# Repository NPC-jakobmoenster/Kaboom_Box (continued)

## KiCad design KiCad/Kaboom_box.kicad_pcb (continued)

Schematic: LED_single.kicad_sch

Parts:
LED104, LED105, LED106: KT-0603R; LED0603-RD; LCSC C2286
R155, R156, R157: 0603WAF2000T5E; R0603; LCSC C8218
U121, U122: 2N7002; SOT-23-3_L2.9-W1.3-P1.90-LS2.4-BR; LCSC C8545

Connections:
/Bottom/LEDs_Bottom/LEDS_discreet/LED_single1/LED_GREEN: U122.1 (G); also elsewhere on the board
/Bottom/LEDs_Bottom/LEDS_discreet/LED_single1/LED_RED: U121.1 (G); also elsewhere on the board
/Bottom/LEDs_Bottom/VDD: R155.2, R156.2, R157.2; also elsewhere on the board
GND: U121.2 (S), U122.2 (S); also elsewhere on the board
unnamed: LED104.2 (A), R155.1
unnamed: LED104.1 (K), LED105.1 (K), U121.3 (D)
unnamed: LED105.2 (A), R156.1
unnamed: LED106.2 (A), R157.1
unnamed: LED106.1 (K), U122.3 (D)

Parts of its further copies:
LED109, LED110, LED111, LED112, LED113, LED114, LED115, LED116, LED117, LED118, LED119, LED120, LED121, LED122, LED123, LED124, LED125, LED126, LED127, LED128, LED129, LED130, LED131, LED132, LED133, LED134, LED135, LED136, LED137, LED138, LED139, LED140, LED141, LED142, LED143, LED144, LED145, LED146, LED147, LED148, LED149, LED150, LED151, LED152, LED153, LED154, LED155, LED156, LED157, LED158, LED159, LED160, LED161, LED162, LED163, LED164, LED165, LED166, LED167, LED168, LED169, LED170, LED171, LED172, LED173, LED174, LED175, LED176, LED177, LED178, LED179, LED180, LED181, LED182, LED183, LED184, LED185, LED186, LED187, LED188, LED189, LED190, LED191, LED192, LED193, LED194, LED195, LED196, LED197, LED198, LED199, LED200, LED201, LED202, LED203, LED204, LED205, LED206, LED207, LED208, LED209, LED210, LED211, LED212, LED213, LED214, LED215, LED216, LED217, LED218, LED219, LED220, LED221, LED222, LED223, LED224, LED225, LED226, LED227, LED228, LED229, LED230, LED231, LED232, LED233, LED234, LED235, LED236, LED237, LED238, LED239, LED240, LED241, LED242, LED243, LED244, LED245, LED246, LED247, LED248, LED249, LED250, LED251, LED252, LED253, LED254, LED255, LED256, LED257, LED258, LED259, LED260, LED261, LED262, LED263, LED264, LED265, LED266, LED267, LED268, LED269, LED270, LED271, LED272, LED273, LED274, LED275, LED276, LED277, LED278, LED279, LED280, LED281, LED282, LED283, LED284, LED285, LED286, LED287, LED288, LED289, LED290, LED291, LED292, LED293, LED294, LED295, LED296, LED297: KT-0603R; LED0603-RD; LCSC C2286
R163, R164, R165, R166, R167, R168, R169, R170, R171, R172, R173, R174, R175, R176, R177, R178, R179, R180, R181, R182, R183, R184, R185, R186, R187, R188, R189, R190, R191, R192, R193, R194, R195, R196, R197, R198, R199, R200, R201, R202, R203, R204, R205, R206, R207, R208, R209, R210, R211, R212, R213, R214, R215, R216, R217, R218, R219, R220, R221, R222, R223, R224, R225, R226, R227, R228, R229, R230, R231, R232, R233, R234, R235, R236, R237, R238, R239, R240, R241, R242, R243, R244, R245, R246, R247, R248, R249, R250, R251, R252, R253, R254, R255, R256, R257, R258, R259, R260, R261, R262, R263, R264, R265, R266, R267, R268, R269, R270, R271, R272, R273, R274, R275, R276, R277, R278, R279, R280, R281, R282, R283, R284, R285, R286, R287, R288, R289, R290, R291, R292, R293, R294, R295, R296, R297, R298, R299, R300, R301, R302, R303, R304, R305, R306, R307, R308, R309, R310, R311, R312, R313, R314, R315, R316, R317, R318, R319, R320, R321, R322, R323, R324, R325, R326, R327, R328, R329, R330, R331, R332, R333, R334, R335, R336, R337, R338, R339, R340, R341, R342, R343, R344, R345, R346, R347, R348, R349, R350, R351: 0603WAF2000T5E; R0603; LCSC C8218
U128, U130, U131, U132, U133, U134, U135, U136, U137, U138, U139, U141, U142, U143, U144, U145, U146, U147, U148, U149, U150, U152, U153, U154, U155, U156, U157, U158, U159, U160, U161, U163, U164, U165, U166, U167, U168, U169, U170, U171, U172, U173, U174, U176, U177, U178, U179, U180, U181, U182, U183, U185, U186, U187, U188, U189, U190, U191, U192, U194, U195, U197, U198, U199, U200, U201, U202, U203, U204, U206, U207, U208, U209, U210, U211, U212, U213, U214, U215, U216, U217, U218, U219, U220, U222, U223, U224, U225, U226, U227, U228, U229, U231, U232, U233, U234, U235, U236, U237, U238, U240, U241, U242, U243, U244, U245, U246, U247, U249, U250, U251, U252, U253, U254, U255, U256, U258, U259, U260, U261, U262, U263, U264, U265, U266, U267: 2N7002; SOT-23-3_L2.9-W1.3-P1.90-LS2.4-BR; LCSC C8545

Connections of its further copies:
/Bottom/LEDs_Bottom/LEDS_discreet2/LED_single1/LED_GREEN: U188.1 (G); also elsewhere on the board
/Bottom/LEDs_Bottom/LEDS_discreet2/LED_single1/LED_RED: U187.1 (G); also elsewhere on the board
/Bottom/LEDs_Bottom/LEDS_discreet2/LED_single2/LED_GREEN: U190.1 (G); also elsewhere on the board
/Bottom/LEDs_Bottom/LEDS_discreet2/LED_single2/LED_RED: U189.1 (G); also elsewhere on the board
/Bottom/LEDs_Bottom/LEDS_discreet2/LED_single3/LED_GREEN: U192.1 (G); also elsewhere on the board
/Bottom/LEDs_Bottom/LEDS_discreet2/LED_single3/LED_RED: U191.1 (G); also elsewhere on the board
/Bottom/LEDs_Bottom/LEDS_discreet2/LED_single/LED_GREEN: U186.1 (G); also elsewhere on the board
/Bottom/LEDs_Bottom/LEDS_discreet2/LED_single/LED_RED: U185.1 (G); also elsewhere on the board
/Bottom/LEDs_Bottom/LEDS_discreet3/LED_single1/LED_GREEN: U144.1 (G); also elsewhere on the board
/Bottom/LEDs_Bottom/LEDS_discreet3/LED_single1/LED_RED: U143.1 (G); also elsewhere on the board
/Bottom/LEDs_Bottom/LEDS_discreet3/LED_single2/LED_GREEN: U146.1 (G); also elsewhere on the board
/Bottom/LEDs_Bottom/LEDS_discreet3/LED_single2/LED_RED: U145.1 (G); also elsewhere on the board
/Bottom/LEDs_Bottom/LEDS_discreet3/LED_single3/LED_GREEN: U148.1 (G); also elsewhere on the board
/Bottom/LEDs_Bottom/LEDS_discreet3/LED_single3/LED_RED: U147.1 (G); also elsewhere on the board
/Bottom/LEDs_Bottom/LEDS_discreet3/LED_single/LED_GREEN: U142.1 (G); also elsewhere on the board
/Bottom/LEDs_Bottom/LEDS_discreet3/LED_single/LED_RED: U141.1 (G); also elsewhere on the board
/Bottom/LEDs_Bottom/LEDS_discreet4/LED_single1/LED_GREEN: U166.1 (G); also elsewhere on the board
/Bottom/LEDs_Bottom/LEDS_discreet4/LED_single1/LED_RED: U165.1 (G); also elsewhere on the board
/Bottom/LEDs_Bottom/LEDS_discreet4/LED_single2/LED_GREEN: U170.1 (G); also elsewhere on the board
/Bottom/LEDs_Bottom/LEDS_discreet4/LED_single2/LED_RED: U169.1 (G); also elsewhere on the board
/Bottom/LEDs_Bottom/LEDS_discreet4/LED_single3/LED_GREEN: U172.1 (G); also elsewhere on the board
/Bottom/LEDs_Bottom/LEDS_discreet4/LED_single3/LED_RED: U171.1 (G); also elsewhere on the board
/Bottom/LEDs_Bottom/LEDS_discreet4/LED_single/LED_GREEN: U164.1 (G); also elsewhere on the board
/Bottom/LEDs_Bottom/LEDS_discreet4/LED_single/LED_RED: U163.1 (G); also elsewhere on the board
/Bottom/LEDs_Bottom/LEDS_discreet5/LED_single1/LED_GREEN: U209.1 (G); also elsewhere on the board
/Bottom/LEDs_Bottom/LEDS_discreet5/LED_single1/LED_RED: U208.1 (G); also elsewhere on the board
/Bottom/LEDs_Bottom/LEDS_discreet5/LED_single2/LED_GREEN: U211.1 (G); also elsewhere on the board
/Bottom/LEDs_Bottom/LEDS_discreet5/LED_single2/LED_RED: U210.1 (G); also elsewhere on the board
/Bottom/LEDs_Bottom/LEDS_discreet5/LED_single3/LED_GREEN: U213.1 (G); also elsewhere on the board
/Bottom/LEDs_Bottom/LEDS_discreet5/LED_single3/LED_RED: U212.1 (G); also elsewhere on the board
/Bottom/LEDs_Bottom/LEDS_discreet5/LED_single/LED_GREEN: U207.1 (G); also elsewhere on the board
/Bottom/LEDs_Bottom/LEDS_discreet5/LED_single/LED_RED: U206.1 (G); also elsewhere on the board
/Bottom/LEDs_Bottom/LEDS_discreet6/LED_single1/LED_GREEN: U225.1 (G); also elsewhere on the board
/Bottom/LEDs_Bottom/LEDS_discreet6/LED_single1/LED_RED: U224.1 (G); also elsewhere on the board
/Bottom/LEDs_Bottom/LEDS_discreet6/LED_single2/LED_GREEN: U227.1 (G); also elsewhere on the board
/Bottom/LEDs_Bottom/LEDS_discreet6/LED_single2/LED_RED: U226.1 (G); also elsewhere on the board
/Bottom/LEDs_Bottom/LEDS_discreet6/LED_single3/LED_GREEN: U229.1 (G); also elsewhere on the board
/Bottom/LEDs_Bottom/LEDS_discreet6/LED_single3/LED_RED: U228.1 (G); also elsewhere on the board
/Bottom/LEDs_Bottom/LEDS_discreet6/LED_single/LED_GREEN: U223.1 (G); also elsewhere on the board
/Bottom/LEDs_Bottom/LEDS_discreet6/LED_single/LED_RED: U222.1 (G); also elsewhere on the board
/Bottom/LEDs_Bottom/LEDS_discreet7/LED_single1/LED_GREEN: U243.1 (G); also elsewhere on the board
/Bottom/LEDs_Bottom/LEDS_discreet7/LED_single1/LED_RED: U242.1 (G); also elsewhere on the board
/Bottom/LEDs_Bottom/LEDS_discreet7/LED_single2/LED_GREEN: U245.1 (G); also elsewhere on the board
/Bottom/LEDs_Bottom/LEDS_discreet7/LED_single2/LED_RED: U244.1 (G); also elsewhere on the board
/Bottom/LEDs_Bottom/LEDS_discreet7/LED_single3/LED_GREEN: U247.1 (G); also elsewhere on the board
/Bottom/LEDs_Bottom/LEDS_discreet7/LED_single3/LED_RED: U246.1 (G); also elsewhere on the board
/Bottom/LEDs_Bottom/LEDS_discreet7/LED_single/LED_GREEN: U241.1 (G); also elsewhere on the board
/Bottom/LEDs_Bottom/LEDS_discreet7/LED_single/LED_RED: U240.1 (G); also elsewhere on the board
/Bottom/LEDs_Bottom/LEDS_discreet8/LED_single1/LED_GREEN: U261.1 (G); also elsewhere on the board
/Bottom/LEDs_Bottom/LEDS_discreet8/LED_single1/LED_RED: U260.1 (G); also elsewhere on the board
/Bottom/LEDs_Bottom/LEDS_discreet8/LED_single2/LED_GREEN: U263.1 (G); also elsewhere on the board
/Bottom/LEDs_Bottom/LEDS_discreet8/LED_single2/LED_RED: U262.1 (G); also elsewhere on the board
/Bottom/LEDs_Bottom/LEDS_discreet8/LED_single3/LED_GREEN: U265.1 (G); also elsewhere on the board
/Bottom/LEDs_Bottom/LEDS_discreet8/LED_single3/LED_RED: U264.1 (G); also elsewhere on the board
/Bottom/LEDs_Bottom/LEDS_discreet8/LED_single/LED_GREEN: U259.1 (G); also elsewhere on the board
/Bottom/LEDs_Bottom/LEDS_discreet8/LED_single/LED_RED: U258.1 (G); also elsewhere on the board
/Bottom/LEDs_Bottom/LEDS_discreet/LED_single2/LED_GREEN: U150.1 (G); also elsewhere on the board
/Bottom/LEDs_Bottom/LEDS_discreet/LED_single2/LED_RED: U149.1 (G); also elsewhere on the board
/Bottom/LEDs_Bottom/LEDS_discreet/LED_single3/LED_GREEN: U168.1 (G); also elsewhere on the board
/Bottom/LEDs_Bottom/LEDS_discreet/LED_single3/LED_RED: U167.1 (G); also elsewhere on the board
/Bottom/LEDs_Bottom/LEDS_discreet/LED_single/LED_GREEN: U128.1 (G); also elsewhere on the board
/Bottom/LEDs_Bottom/LEDS_discreet/LED_single/LED_RED: U267.1 (G); also elsewhere on the board
/Bottom/LEDs_Bottom/VDD: R163.2, R164.2, R165.2, R181.2, R182.2, R183.2, R184.2, R185.2, R186.2, R187.2, R188.2, R189.2, R190.2, R191.2, R192.2, R193.2, R194.2, R195.2, R211.2, R212.2, R213.2, R214.2, R215.2, R216.2, R217.2, R218.2, R219.2, R220.2, R221.2, R222.2, R223.2, R224.2, R225.2, R241.2, R242.2, R243.2, R244.2, R245.2, R246.2, R247.2, R248.2, R249.2, R250.2, R251.2, R252.2, R268.2, R269.2, R270.2, R271.2, R272.2, R273.2, R274.2, R275.2, R276.2, R277.2, R278.2, R279.2, R292.2, R293.2, R294.2, R295.2, R296.2, R297.2, R298.2, R299.2, R300.2, R301.2, R302.2, R303.2, R316.2, R317.2, R318.2, R319.2, R320.2, R321.2, R322.2, R323.2, R324.2, R325.2, R326.2, R327.2, R340.2, R341.2, R342.2, R343.2, R344.2, R345.2, R346.2, R347.2, R348.2, R349.2, R350.2, R351.2; also elsewhere on the board
/Top/GND: U130.2 (S), U131.2 (S), U132.2 (S), U133.2 (S), U134.2 (S), U135.2 (S), U136.2 (S), U137.2 (S), U138.2 (S), U139.2 (S), U152.2 (S), U153.2 (S), U154.2 (S), U155.2 (S), U156.2 (S), U157.2 (S), U158.2 (S), U159.2 (S), U160.2 (S), U161.2 (S), U173.2 (S), U174.2 (S), U176.2 (S), U177.2 (S), U178.2 (S), U179.2 (S), U180.2 (S), U181.2 (S), U182.2 (S), U183.2 (S), U194.2 (S), U195.2 (S), U197.2 (S), U198.2 (S), U199.2 (S), U200.2 (S), U201.2 (S), U202.2 (S), U203.2 (S), U204.2 (S), U214.2 (S), U215.2 (S), U216.2 (S), U217.2 (S), U218.2 (S), U219.2 (S), U220.2 (S), U231.2 (S), U232.2 (S), U233.2 (S), U234.2 (S), U235.2 (S), U236.2 (S), U237.2 (S), U238.2 (S), U249.2 (S), U250.2 (S), U251.2 (S), U252.2 (S), U253.2 (S), U254.2 (S), U255.2 (S), U256.2 (S), U266.2 (S); also elsewhere on the board
/Top/LEDs_Bottom/LEDS_discreet2/LED_single1/LED_GREEN: U179.1 (G); also elsewhere on the board
/Top/LEDs_Bottom/LEDS_discreet2/LED_single1/LED_RED: U178.1 (G); also elsewhere on the board
/Top/LEDs_Bottom/LEDS_discreet2/LED_single2/LED_GREEN: U181.1 (G); also elsewhere on the board
/Top/LEDs_Bottom/LEDS_discreet2/LED_single2/LED_RED: U180.1 (G); also elsewhere on the board
/Top/LEDs_Bottom/LEDS_discreet2/LED_single3/LED_GREEN: U183.1 (G); also elsewhere on the board
/Top/LEDs_Bottom/LEDS_discreet2/LED_single3/LED_RED: U182.1 (G); also elsewhere on the board
/Top/LEDs_Bottom/LEDS_discreet2/LED_single/LED_GREEN: U177.1 (G); also elsewhere on the board
/Top/LEDs_Bottom/LEDS_discreet2/LED_single/LED_RED: U176.1 (G); also elsewhere on the board
/Top/LEDs_Bottom/LEDS_discreet3/LED_single1/LED_GREEN: U133.1 (G); also elsewhere on the board
/Top/LEDs_Bottom/LEDS_discreet3/LED_single1/LED_RED: U132.1 (G); also elsewhere on the board
/Top/LEDs_Bottom/LEDS_discreet3/LED_single2/LED_GREEN: U135.1 (G); also elsewhere on the board
/Top/LEDs_Bottom/LEDS_discreet3/LED_single2/LED_RED: U134.1 (G); also elsewhere on the board
/Top/LEDs_Bottom/LEDS_discreet3/LED_single3/LED_GREEN: U137.1 (G); also elsewhere on the board
/Top/LEDs_Bottom/LEDS_discreet3/LED_single3/LED_RED: U136.1 (G); also elsewhere on the board
/Top/LEDs_Bottom/LEDS_discreet3/LED_single/LED_GREEN: U131.1 (G); also elsewhere on the board
/Top/LEDs_Bottom/LEDS_discreet3/LED_single/LED_RED: U130.1 (G); also elsewhere on the board
/Top/LEDs_Bottom/LEDS_discreet4/LED_single1/LED_GREEN: U155.1 (G); also elsewhere on the board
/Top/LEDs_Bottom/LEDS_discreet4/LED_single1/LED_RED: U154.1 (G); also elsewhere on the board
/Top/LEDs_Bottom/LEDS_discreet4/LED_single2/LED_GREEN: U157.1 (G); also elsewhere on the board
/Top/LEDs_Bottom/LEDS_discreet4/LED_single2/LED_RED: U156.1 (G); also elsewhere on the board
/Top/LEDs_Bottom/LEDS_discreet4/LED_single3/LED_GREEN: U159.1 (G); also elsewhere on the board
/Top/LEDs_Bottom/LEDS_discreet4/LED_single3/LED_RED: U158.1 (G); also elsewhere on the board
/Top/LEDs_Bottom/LEDS_discreet4/LED_single/LED_GREEN: U153.1 (G); also elsewhere on the board
/Top/LEDs_Bottom/LEDS_discreet4/LED_single/LED_RED: U152.1 (G); also elsewhere on the board
/Top/LEDs_Bottom/LEDS_discreet5/LED_single1/LED_GREEN: U200.1 (G); also elsewhere on the board
/Top/LEDs_Bottom/LEDS_discreet5/LED_single1/LED_RED: U199.1 (G); also elsewhere on the board
/Top/LEDs_Bottom/LEDS_discreet5/LED_single2/LED_GREEN: U202.1 (G); also elsewhere on the board
/Top/LEDs_Bottom/LEDS_discreet5/LED_single2/LED_RED: U201.1 (G); also elsewhere on the board
/Top/LEDs_Bottom/LEDS_discreet5/LED_single3/LED_GREEN: U204.1 (G); also elsewhere on the board
/Top/LEDs_Bottom/LEDS_discreet5/LED_single3/LED_RED: U203.1 (G); also elsewhere on the board
/Top/LEDs_Bottom/LEDS_discreet5/LED_single/LED_GREEN: U198.1 (G); also elsewhere on the board
/Top/LEDs_Bottom/LEDS_discreet5/LED_single/LED_RED: U197.1 (G); also elsewhere on the board
/Top/LEDs_Bottom/LEDS_discreet6/LED_single1/LED_GREEN: U216.1 (G); also elsewhere on the board
/Top/LEDs_Bottom/LEDS_discreet6/LED_single1/LED_RED: U215.1 (G); also elsewhere on the board
/Top/LEDs_Bottom/LEDS_discreet6/LED_single2/LED_GREEN: U218.1 (G); also elsewhere on the board
/Top/LEDs_Bottom/LEDS_discreet6/LED_single2/LED_RED: U217.1 (G); also elsewhere on the board
/Top/LEDs_Bottom/LEDS_discreet6/LED_single3/LED_GREEN: U220.1 (G); also elsewhere on the board
/Top/LEDs_Bottom/LEDS_discreet6/LED_single3/LED_RED: U219.1 (G); also elsewhere on the board
/Top/LEDs_Bottom/LEDS_discreet6/LED_single/LED_GREEN: U214.1 (G); also elsewhere on the board
/Top/LEDs_Bottom/LEDS_discreet6/LED_single/LED_RED: U194.1 (G); also elsewhere on the board
/Top/LEDs_Bottom/LEDS_discreet7/LED_single1/LED_GREEN: U234.1 (G); also elsewhere on the board
/Top/LEDs_Bottom/LEDS_discreet7/LED_single1/LED_RED: U233.1 (G); also elsewhere on the board
/Top/LEDs_Bottom/LEDS_discreet7/LED_single2/LED_GREEN: U236.1 (G); also elsewhere on the board
/Top/LEDs_Bottom/LEDS_discreet7/LED_single2/LED_RED: U235.1 (G); also elsewhere on the board
/Top/LEDs_Bottom/LEDS_discreet7/LED_single3/LED_GREEN: U238.1 (G); also elsewhere on the board
/Top/LEDs_Bottom/LEDS_discreet7/LED_single3/LED_RED: U237.1 (G); also elsewhere on the board
/Top/LEDs_Bottom/LEDS_discreet7/LED_single/LED_GREEN: U232.1 (G); also elsewhere on the board
/Top/LEDs_Bottom/LEDS_discreet7/LED_single/LED_RED: U231.1 (G); also elsewhere on the board
/Top/LEDs_Bottom/LEDS_discreet8/LED_single1/LED_GREEN: U252.1 (G); also elsewhere on the board
/Top/LEDs_Bottom/LEDS_discreet8/LED_single1/LED_RED: U251.1 (G); also elsewhere on the board
/Top/LEDs_Bottom/LEDS_discreet8/LED_single2/LED_GREEN: U254.1 (G); also elsewhere on the board
/Top/LEDs_Bottom/LEDS_discreet8/LED_single2/LED_RED: U253.1 (G); also elsewhere on the board
/Top/LEDs_Bottom/LEDS_discreet8/LED_single3/LED_GREEN: U256.1 (G); also elsewhere on the board
/Top/LEDs_Bottom/LEDS_discreet8/LED_single3/LED_RED: U255.1 (G); also elsewhere on the board
/Top/LEDs_Bottom/LEDS_discreet8/LED_single/LED_GREEN: U250.1 (G); also elsewhere on the board
/Top/LEDs_Bottom/LEDS_discreet8/LED_single/LED_RED: U249.1 (G); also elsewhere on the board
/Top/LEDs_Bottom/LEDS_discreet/LED_single1/LED_GREEN: U139.1 (G); also elsewhere on the board
/Top/LEDs_Bottom/LEDS_discreet/LED_single1/LED_RED: U138.1 (G); also elsewhere on the board
/Top/LEDs_Bottom/LEDS_discreet/LED_single2/LED_GREEN: U161.1 (G); also elsewhere on the board
/Top/LEDs_Bottom/LEDS_discreet/LED_single2/LED_RED: U160.1 (G); also elsewhere on the board
/Top/LEDs_Bottom/LEDS_discreet/LED_single3/LED_GREEN: U174.1 (G); also elsewhere on the board
/Top/LEDs_Bottom/LEDS_discreet/LED_single3/LED_RED: U173.1 (G); also elsewhere on the board
/Top/LEDs_Bottom/LEDS_discreet/LED_single/LED_GREEN: U195.1 (G); also elsewhere on the board
/Top/LEDs_Bottom/LEDS_discreet/LED_single/LED_RED: U266.1 (G); also elsewhere on the board
/Top/VDD: R166.2, R167.2, R168.2, R169.2, R170.2, R171.2, R172.2, R173.2, R174.2, R175.2, R176.2, R177.2, R178.2, R179.2, R180.2, R196.2, R197.2, R198.2, R199.2, R200.2, R201.2, R202.2, R203.2, R204.2, R205.2, R206.2, R207.2, R208.2, R209.2, R210.2, R226.2, R227.2, R228.2, R229.2, R230.2, R231.2, R232.2, R233.2, R234.2, R235.2, R236.2, R237.2, R238.2, R239.2, R240.2, R253.2, R254.2, R255.2, R256.2, R257.2, R258.2, R259.2, R260.2, R261.2, R262.2, R263.2, R264.2, R265.2, R266.2, R267.2, R280.2, R281.2, R282.2, R283.2, R284.2, R285.2, R286.2, R287.2, R288.2, R289.2, R290.2, R291.2, R304.2, R305.2, R306.2, R307.2, R308.2, R309.2, R310.2, R311.2, R312.2, R313.2, R314.2, R315.2, R328.2, R329.2, R330.2, R331.2, R332.2, R333.2, R334.2, R335.2, R336.2, R337.2, R338.2, R339.2; also elsewhere on the board
GND: U128.2 (S), U141.2 (S), U142.2 (S), U143.2 (S), U144.2 (S), U145.2 (S), U146.2 (S), U147.2 (S), U148.2 (S), U149.2 (S), U150.2 (S), U163.2 (S), U164.2 (S), U165.2 (S), U166.2 (S), U167.2 (S), U168.2 (S), U169.2 (S), U170.2 (S), U171.2 (S), U172.2 (S), U185.2 (S), U186.2 (S), U187.2 (S), U188.2 (S), U189.2 (S), U190.2 (S), U191.2 (S), U192.2 (S), U206.2 (S), U207.2 (S), U208.2 (S), U209.2 (S), U210.2 (S), U211.2 (S), U212.2 (S), U213.2 (S), U222.2 (S), U223.2 (S), U224.2 (S), U225.2 (S), U226.2 (S), U227.2 (S), U228.2 (S), U229.2 (S), U240.2 (S), U241.2 (S), U242.2 (S), U243.2 (S), U244.2 (S), U245.2 (S), U246.2 (S), U247.2 (S), U258.2 (S), U259.2 (S), U260.2 (S), U261.2 (S), U262.2 (S), U263.2 (S), U264.2 (S), U265.2 (S), U267.2 (S); also elsewhere on the board
unnamed: LED109.2 (A), R163.1
unnamed: LED109.1 (K), LED110.1 (K), U267.3 (D)
unnamed: LED110.2 (A), R164.1
unnamed: LED111.2 (A), R165.1
unnamed: LED111.1 (K), U128.3 (D)
unnamed: LED112.2 (A), R166.1
unnamed: LED112.1 (K), LED113.1 (K), U130.3 (D)
unnamed: LED113.2 (A), R167.1
unnamed: LED114.2 (A), R168.1
unnamed: LED114.1 (K), U131.3 (D)
unnamed: LED115.2 (A), R169.1
unnamed: LED115.1 (K), LED116.1 (K), U132.3 (D)
unnamed: LED116.2 (A), R170.1
unnamed: LED117.2 (A), R171.1
unnamed: LED117.1 (K), U133.3 (D)
unnamed: LED118.2 (A), R172.1
unnamed: LED118.1 (K), LED119.1 (K), U134.3 (D)
unnamed: LED119.2 (A), R173.1
unnamed: LED120.2 (A), R174.1
unnamed: LED120.1 (K), U135.3 (D)
unnamed: LED121.2 (A), R175.1
unnamed: LED121.1 (K), LED122.1 (K), U136.3 (D)
unnamed: LED122.2 (A), R176.1
unnamed: LED123.2 (A), R177.1
unnamed: LED123.1 (K), U137.3 (D)
unnamed: LED124.2 (A), R178.1
unnamed: LED124.1 (K), LED125.1 (K), U138.3 (D)
unnamed: LED125.2 (A), R179.1
unnamed: LED126.2 (A), R180.1
unnamed: LED126.1 (K), U139.3 (D)
unnamed: LED127.2 (A), R181.1
unnamed: LED127.1 (K), LED128.1 (K), U141.3 (D)
unnamed: LED128.2 (A), R182.1
unnamed: LED129.2 (A), R183.1
unnamed: LED129.1 (K), U142.3 (D)
unnamed: LED130.2 (A), R184.1
unnamed: LED130.1 (K), LED131.1 (K), U143.3 (D)
unnamed: LED131.2 (A), R185.1
unnamed: LED132.2 (A), R186.1
unnamed: LED132.1 (K), U144.3 (D)
unnamed: LED133.2 (A), R187.1
unnamed: LED133.1 (K), LED134.1 (K), U145.3 (D)
unnamed: LED134.2 (A), R188.1
unnamed: LED135.2 (A), R189.1
unnamed: LED135.1 (K), U146.3 (D)
unnamed: LED136.2 (A), R190.1
unnamed: LED136.1 (K), LED137.1 (K), U147.3 (D)
unnamed: LED137.2 (A), R191.1
unnamed: LED138.2 (A), R192.1
unnamed: LED138.1 (K), U148.3 (D)
unnamed: LED139.2 (A), R193.1
unnamed: LED139.1 (K), LED140.1 (K), U149.3 (D)
unnamed: LED140.2 (A), R194.1
unnamed: LED141.2 (A), R195.1
unnamed: LED141.1 (K), U150.3 (D)
unnamed: LED142.2 (A), R196.1
unnamed: LED142.1 (K), LED143.1 (K), U152.3 (D)
unnamed: LED143.2 (A), R197.1
unnamed: LED144.2 (A), R198.1
unnamed: LED144.1 (K), U153.3 (D)
unnamed: LED145.2 (A), R199.1
unnamed: LED145.1 (K), LED146.1 (K), U154.3 (D)
unnamed: LED146.2 (A), R200.1
unnamed: LED147.2 (A), R201.1
unnamed: LED147.1 (K), U155.3 (D)
unnamed: LED148.2 (A), R202.1
unnamed: LED148.1 (K), LED149.1 (K), U156.3 (D)
unnamed: LED149.2 (A), R203.1
unnamed: LED150.2 (A), R204.1
unnamed: LED150.1 (K), U157.3 (D)
unnamed: LED151.2 (A), R205.1
unnamed: LED151.1 (K), LED152.1 (K), U158.3 (D)
unnamed: LED152.2 (A), R206.1
unnamed: LED153.2 (A), R207.1
unnamed: LED153.1 (K), U159.3 (D)
unnamed: LED154.2 (A), R208.1
unnamed: LED154.1 (K), LED155.1 (K), U160.3 (D)
unnamed: LED155.2 (A), R209.1
unnamed: LED156.2 (A), R210.1
unnamed: LED156.1 (K), U161.3 (D)
unnamed: LED157.2 (A), R211.1
unnamed: LED157.1 (K), LED158.1 (K), U163.3 (D)
unnamed: LED158.2 (A), R212.1
unnamed: LED159.2 (A), R213.1
unnamed: LED159.1 (K), U164.3 (D)
unnamed: LED160.2 (A), R214.1
unnamed: LED160.1 (K), LED161.1 (K), U165.3 (D)
unnamed: LED161.2 (A), R215.1
unnamed: LED162.2 (A), R216.1
unnamed: LED162.1 (K), U166.3 (D)
unnamed: LED163.2 (A), R217.1
unnamed: LED163.1 (K), LED164.1 (K), U167.3 (D)
unnamed: LED164.2 (A), R218.1
unnamed: LED165.2 (A), R219.1
unnamed: LED165.1 (K), U168.3 (D)
unnamed: LED166.2 (A), R220.1
unnamed: LED166.1 (K), LED167.1 (K), U169.3 (D)
unnamed: LED167.2 (A), R221.1
unnamed: LED168.2 (A), R222.1
unnamed: LED168.1 (K), U170.3 (D)
unnamed: LED169.2 (A), R223.1
unnamed: LED169.1 (K), LED170.1 (K), U171.3 (D)
unnamed: LED170.2 (A), R224.1
unnamed: LED171.2 (A), R225.1
unnamed: LED171.1 (K), U172.3 (D)
unnamed: LED172.2 (A), R226.1
unnamed: LED172.1 (K), LED173.1 (K), U173.3 (D)
unnamed: LED173.2 (A), R227.1
unnamed: LED174.2 (A), R228.1
unnamed: LED174.1 (K), U174.3 (D)
unnamed: LED175.2 (A), R229.1
unnamed: LED175.1 (K), LED176.1 (K), U176.3 (D)
unnamed: LED176.2 (A), R230.1
unnamed: LED177.2 (A), R231.1
unnamed: LED177.1 (K), U177.3 (D)
unnamed: LED178.2 (A), R232.1
unnamed: LED178.1 (K), LED179.1 (K), U178.3 (D)
unnamed: LED179.2 (A), R233.1
unnamed: LED180.2 (A), R234.1
unnamed: LED180.1 (K), U179.3 (D)
unnamed: LED181.2 (A), R235.1
unnamed: LED181.1 (K), LED182.1 (K), U180.3 (D)
unnamed: LED182.2 (A), R236.1
unnamed: LED183.2 (A), R237.1
unnamed: LED183.1 (K), U181.3 (D)
unnamed: LED184.2 (A), R238.1
unnamed: LED184.1 (K), LED185.1 (K), U182.3 (D)
unnamed: LED185.2 (A), R239.1
unnamed: LED186.2 (A), R240.1
unnamed: LED186.1 (K), U183.3 (D)
unnamed: LED187.2 (A), R241.1
unnamed: LED187.1 (K), LED188.1 (K), U185.3 (D)
unnamed: LED188.2 (A), R242.1
unnamed: LED189.2 (A), R243.1
unnamed: LED189.1 (K), U186.3 (D)
unnamed: LED190.2 (A), R244.1
unnamed: LED190.1 (K), LED191.1 (K), U187.3 (D)
unnamed: LED191.2 (A), R245.1
unnamed: LED192.2 (A), R246.1
unnamed: LED192.1 (K), U188.3 (D)
unnamed: LED193.2 (A), R247.1
unnamed: LED193.1 (K), LED194.1 (K), U189.3 (D)
unnamed: LED194.2 (A), R248.1
unnamed: LED195.2 (A), R249.1
unnamed: LED195.1 (K), U190.3 (D)
unnamed: LED196.2 (A), R250.1
unnamed: LED196.1 (K), LED197.1 (K), U191.3 (D)
unnamed: LED197.2 (A), R251.1
unnamed: LED198.2 (A), R252.1
unnamed: LED198.1 (K), U192.3 (D)
unnamed: LED199.2 (A), R253.1
unnamed: LED199.1 (K), LED200.1 (K), U266.3 (D)
unnamed: LED200.2 (A), R254.1
unnamed: LED201.2 (A), R255.1
unnamed: LED201.1 (K), U195.3 (D)
unnamed: LED202.2 (A), R256.1
unnamed: LED202.1 (K), LED203.1 (K), U197.3 (D)
unnamed: LED203.2 (A), R257.1
unnamed: LED204.2 (A), R258.1
unnamed: LED204.1 (K), U198.3 (D)
unnamed: LED205.2 (A), R259.1
unnamed: LED205.1 (K), LED206.1 (K), U199.3 (D)
unnamed: LED206.2 (A), R260.1
unnamed: LED207.2 (A), R261.1
unnamed: LED207.1 (K), U200.3 (D)
unnamed: LED208.2 (A), R262.1
unnamed: LED208.1 (K), LED209.1 (K), U201.3 (D)
unnamed: LED209.2 (A), R263.1
unnamed: LED210.2 (A), R264.1
unnamed: LED210.1 (K), U202.3 (D)
unnamed: LED211.2 (A), R265.1
unnamed: LED211.1 (K), LED212.1 (K), U203.3 (D)
unnamed: LED212.2 (A), R266.1
unnamed: LED213.2 (A), R267.1
unnamed: LED213.1 (K), U204.3 (D)
unnamed: LED214.2 (A), R268.1
unnamed: LED214.1 (K), LED215.1 (K), U206.3 (D)
unnamed: LED215.2 (A), R269.1
unnamed: LED216.2 (A), R270.1
unnamed: LED216.1 (K), U207.3 (D)
unnamed: LED217.2 (A), R271.1
unnamed: LED217.1 (K), LED218.1 (K), U208.3 (D)
unnamed: LED218.2 (A), R272.1
unnamed: LED219.2 (A), R273.1
unnamed: LED219.1 (K), U209.3 (D)
unnamed: LED220.2 (A), R274.1
unnamed: LED220.1 (K), LED221.1 (K), U210.3 (D)
unnamed: LED221.2 (A), R275.1
unnamed: LED222.2 (A), R276.1
unnamed: LED222.1 (K), U211.3 (D)
unnamed: LED223.2 (A), R277.1
unnamed: LED223.1 (K), LED224.1 (K), U212.3 (D)
unnamed: LED224.2 (A), R278.1
unnamed: LED225.2 (A), R279.1
unnamed: LED225.1 (K), U213.3 (D)
unnamed: LED226.2 (A), R280.1
unnamed: LED226.1 (K), LED227.1 (K), U194.3 (D)
unnamed: LED227.2 (A), R281.1
unnamed: LED228.2 (A), R282.1
unnamed: LED228.1 (K), U214.3 (D)
unnamed: LED229.2 (A), R283.1
unnamed: LED229.1 (K), LED230.1 (K), U215.3 (D)
unnamed: LED230.2 (A), R284.1
unnamed: LED231.2 (A), R285.1
unnamed: LED231.1 (K), U216.3 (D)
unnamed: LED232.2 (A), R286.1
unnamed: LED232.1 (K), LED233.1 (K), U217.3 (D)
unnamed: LED233.2 (A), R287.1
unnamed: LED234.2 (A), R288.1
unnamed: LED234.1 (K), U218.3 (D)
unnamed: LED235.2 (A), R289.1
unnamed: LED235.1 (K), LED236.1 (K), U219.3 (D)
unnamed: LED236.2 (A), R290.1
unnamed: LED237.2 (A), R291.1
unnamed: LED237.1 (K), U220.3 (D)
unnamed: LED238.2 (A), R292.1
unnamed: LED238.1 (K), LED239.1 (K), U222.3 (D)
unnamed: LED239.2 (A), R293.1
unnamed: LED240.2 (A), R294.1
unnamed: LED240.1 (K), U223.3 (D)
unnamed: LED241.2 (A), R295.1
unnamed: LED241.1 (K), LED242.1 (K), U224.3 (D)
unnamed: LED242.2 (A), R296.1
unnamed: LED243.2 (A), R297.1
unnamed: LED243.1 (K), U225.3 (D)
unnamed: LED244.2 (A), R298.1
unnamed: LED244.1 (K), LED245.1 (K), U226.3 (D)
unnamed: LED245.2 (A), R299.1
unnamed: LED246.2 (A), R300.1
unnamed: LED246.1 (K), U227.3 (D)
unnamed: LED247.2 (A), R301.1
unnamed: LED247.1 (K), LED248.1 (K), U228.3 (D)
unnamed: LED248.2 (A), R302.1
unnamed: LED249.2 (A), R303.1
unnamed: LED249.1 (K), U229.3 (D)
unnamed: LED250.2 (A), R304.1
unnamed: LED250.1 (K), LED251.1 (K), U231.3 (D)
unnamed: LED251.2 (A), R305.1
unnamed: LED252.2 (A), R306.1
unnamed: LED252.1 (K), U232.3 (D)
unnamed: LED253.2 (A), R307.1
unnamed: LED253.1 (K), LED254.1 (K), U233.3 (D)
unnamed: LED254.2 (A), R308.1
unnamed: LED255.2 (A), R309.1
unnamed: LED255.1 (K), U234.3 (D)
unnamed: LED256.2 (A), R310.1
unnamed: LED256.1 (K), LED257.1 (K), U235.3 (D)
unnamed: LED257.2 (A), R311.1
unnamed: LED258.2 (A), R312.1
unnamed: LED258.1 (K), U236.3 (D)
unnamed: LED259.2 (A), R313.1
unnamed: LED259.1 (K), LED260.1 (K), U237.3 (D)
unnamed: LED260.2 (A), R314.1
unnamed: LED261.2 (A), R315.1
unnamed: LED261.1 (K), U238.3 (D)
unnamed: LED262.2 (A), R316.1
unnamed: LED262.1 (K), LED263.1 (K), U240.3 (D)
unnamed: LED263.2 (A), R317.1
unnamed: LED264.2 (A), R318.1
unnamed: LED264.1 (K), U241.3 (D)
unnamed: LED265.2 (A), R319.1
unnamed: LED265.1 (K), LED266.1 (K), U242.3 (D)
unnamed: LED266.2 (A), R320.1
unnamed: LED267.2 (A), R321.1
unnamed: LED267.1 (K), U243.3 (D)
unnamed: LED268.2 (A), R322.1
unnamed: LED268.1 (K), LED269.1 (K), U244.3 (D)
unnamed: LED269.2 (A), R323.1
unnamed: LED270.2 (A), R324.1
unnamed: LED270.1 (K), U245.3 (D)
unnamed: LED271.2 (A), R325.1
unnamed: LED271.1 (K), LED272.1 (K), U246.3 (D)
unnamed: LED272.2 (A), R326.1
unnamed: LED273.2 (A), R327.1
unnamed: LED273.1 (K), U247.3 (D)
unnamed: LED274.2 (A), R328.1
unnamed: LED274.1 (K), LED275.1 (K), U249.3 (D)
unnamed: LED275.2 (A), R329.1
unnamed: LED276.2 (A), R330.1
unnamed: LED276.1 (K), U250.3 (D)
unnamed: LED277.2 (A), R331.1
unnamed: LED277.1 (K), LED278.1 (K), U251.3 (D)
unnamed: LED278.2 (A), R332.1
unnamed: LED279.2 (A), R333.1
unnamed: LED279.1 (K), U252.3 (D)
unnamed: LED280.2 (A), R334.1
unnamed: LED280.1 (K), LED281.1 (K), U253.3 (D)
unnamed: LED281.2 (A), R335.1
unnamed: LED282.2 (A), R336.1
unnamed: LED282.1 (K), U254.3 (D)
unnamed: LED283.2 (A), R337.1
unnamed: LED283.1 (K), LED284.1 (K), U255.3 (D)
unnamed: LED284.2 (A), R338.1
unnamed: LED285.2 (A), R339.1
unnamed: LED285.1 (K), U256.3 (D)
unnamed: LED286.2 (A), R340.1
unnamed: LED286.1 (K), LED287.1 (K), U258.3 (D)
unnamed: LED287.2 (A), R341.1
unnamed: LED288.2 (A), R342.1
unnamed: LED288.1 (K), U259.3 (D)
unnamed: LED289.2 (A), R343.1
unnamed: LED289.1 (K), LED290.1 (K), U260.3 (D)
unnamed: LED290.2 (A), R344.1
unnamed: LED291.2 (A), R345.1
unnamed: LED291.1 (K), U261.3 (D)
unnamed: LED292.2 (A), R346.1
unnamed: LED292.1 (K), LED293.1 (K), U262.3 (D)
unnamed: LED293.2 (A), R347.1
unnamed: LED294.2 (A), R348.1
unnamed: LED294.1 (K), U263.3 (D)
unnamed: LED295.2 (A), R349.1
unnamed: LED295.1 (K), LED296.1 (K), U264.3 (D)
unnamed: LED296.2 (A), R350.1
unnamed: LED297.2 (A), R351.1
unnamed: LED297.1 (K), U265.3 (D)

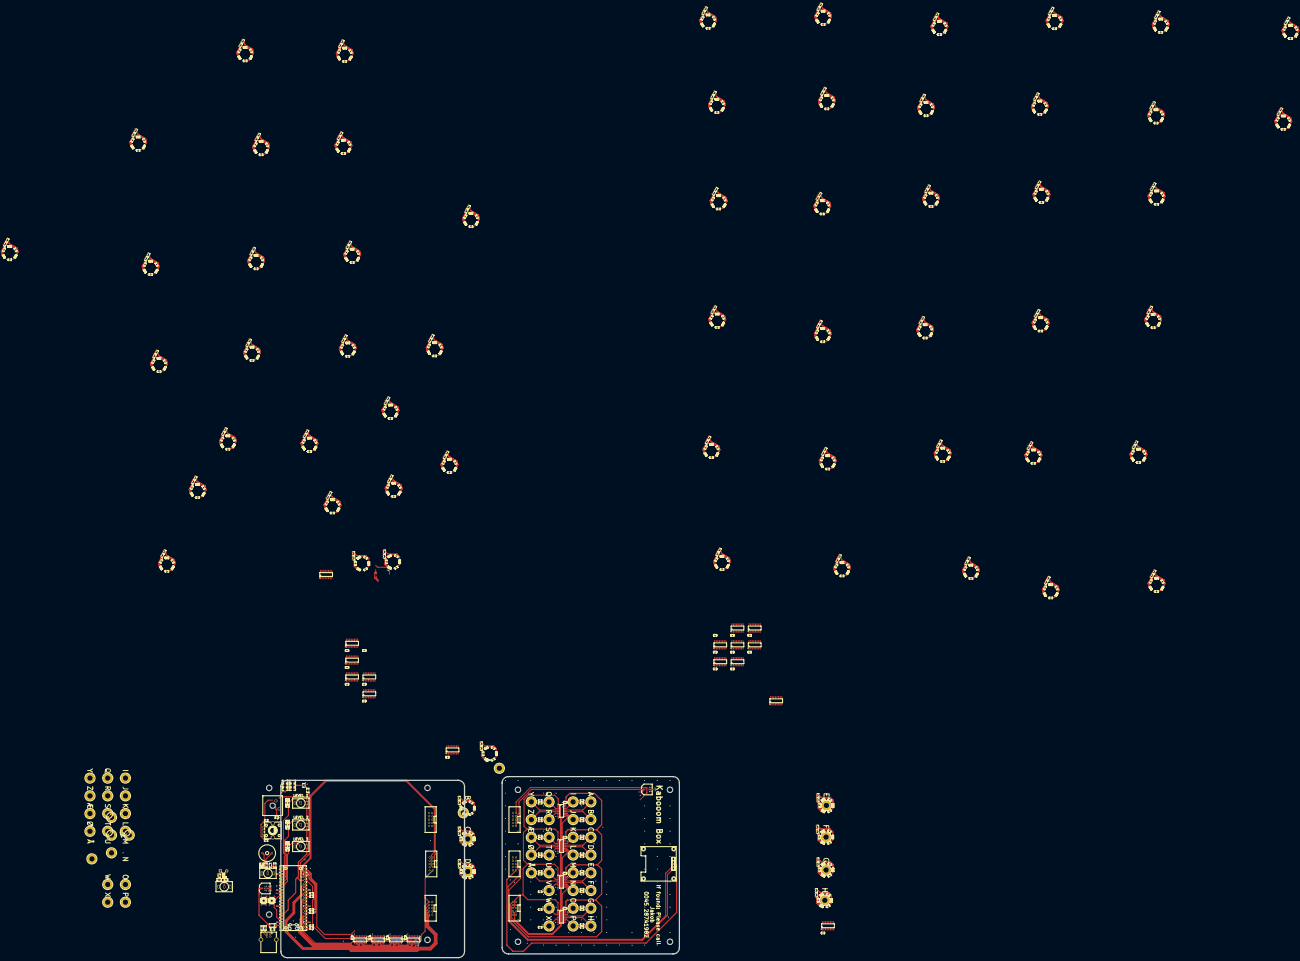
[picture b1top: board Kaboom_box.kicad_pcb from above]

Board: 2 copper layers, 723 parts (1 on the bottom side), 592 nets.
